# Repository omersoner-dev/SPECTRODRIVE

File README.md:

# 🚀 SpectroDrive – Smart Light Following Robot

SpectroDrive is a multi-functional embedded robotics project integrating sensing, control, and wireless communication into a compact system.

---

## 🎯 Project Overview

This robot is capable of:

* Tracking and following light sources
* Performing interactive LED-based behaviors
* Detecting external disturbances (tilt)
* Securing itself with a password-based system
* Being controlled wirelessly via Bluetooth

---

## ⚙️ System Features

* 🔆 Light Following Mode
* 👋 Greeting Mode (LED animation)
* 🚨 Tilt-based Security System
* 🔐 Dual-stage password protection
* 📡 Bluetooth Control (HC-05)
* 📟 LCD Interface
* 🔊 Buzzer Alert System

---

## 🧩 Project Structure

```text
Firmware/
 └── Arduino/
      └── Spectrodrive.ino

Software/
 └── MobileApp/apk/
      └── Spectrodrive.apk

hardware/
 ├── BOM/
 ├── PCB/
 ├── schematic/
 └── images/
```

---

## 🔧 Hardware

Full hardware design including schematic, PCB, and BOM:

👉 [Hardware Documentation](hardware/README.md)

---

## ⚙️ Firmware

Arduino-based embedded control system:

👉 [Firmware Files](Firmware/Arduino/)

---

## 📱 Mobile Application

Bluetooth-based control interface:

👉 [Mobile App](Software/MobileApp/)

---

## 📸 Preview

### PCB Design

### 3D View

---

## 🛠️ Technologies

* KiCad (PCB & schematic)
* Arduino (Embedded control)
* UART / ADC / GPIO
* Bluetooth (HC-05)

---

## 🎯 Purpose

Developed to gain hands-on experience in:

* Embedded systems
* PCB design
* Robotics integration
* Real-time control systems

---

## 🚀 Future Improvements

* Mobile UI enhancements
* Autonomous navigation
* Advanced control algorithms
* IoT integration

---

## 📌 Author

Electrical & Electronics Engineering student focused on embedded systems and robotics.

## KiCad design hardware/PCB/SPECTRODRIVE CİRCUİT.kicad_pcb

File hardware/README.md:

## 🔧 Hardware Design – SpectroDrive

This section contains the complete hardware design of the SpectroDrive smart robot, including schematic design, PCB layout, and bill of materials.

---

### 🧠 System Overview

The hardware system is built around a microcontroller-based architecture and integrates multiple sensing and control modules:

* Light tracking sensors (LDR)
* Ultrasonic distance sensor (HC-SR04)
* Motor driver (L298N)
* Bluetooth module (HC-05)
* LCD display
* Tilt sensor and buzzer for safety alerts

---

### 📐 Schematic

The schematic includes all sensor interfaces, power distribution, and control logic connections.

---

### 🧩 PCB Layout

Custom PCB was designed in KiCad, including routing, footprint selection, and optimized layout for embedded system integration.

---

### 🧱 3D View

3D visualization of the PCB showing component placement and physical structure.

---

### 📦 Bill of Materials (BOM)

The complete list of components can be found in:

* `BOM/bom.xlsx`
* `BOM/bom.csv`

---

### 🛠️ Design Tools

* KiCad (Schematic & PCB Design)
* Custom libraries for specific modules

---

### 🎯 Notes

This hardware was developed as part of a Teknofest-oriented embedded systems project, focusing on modularity, expandability, and real-world testing.

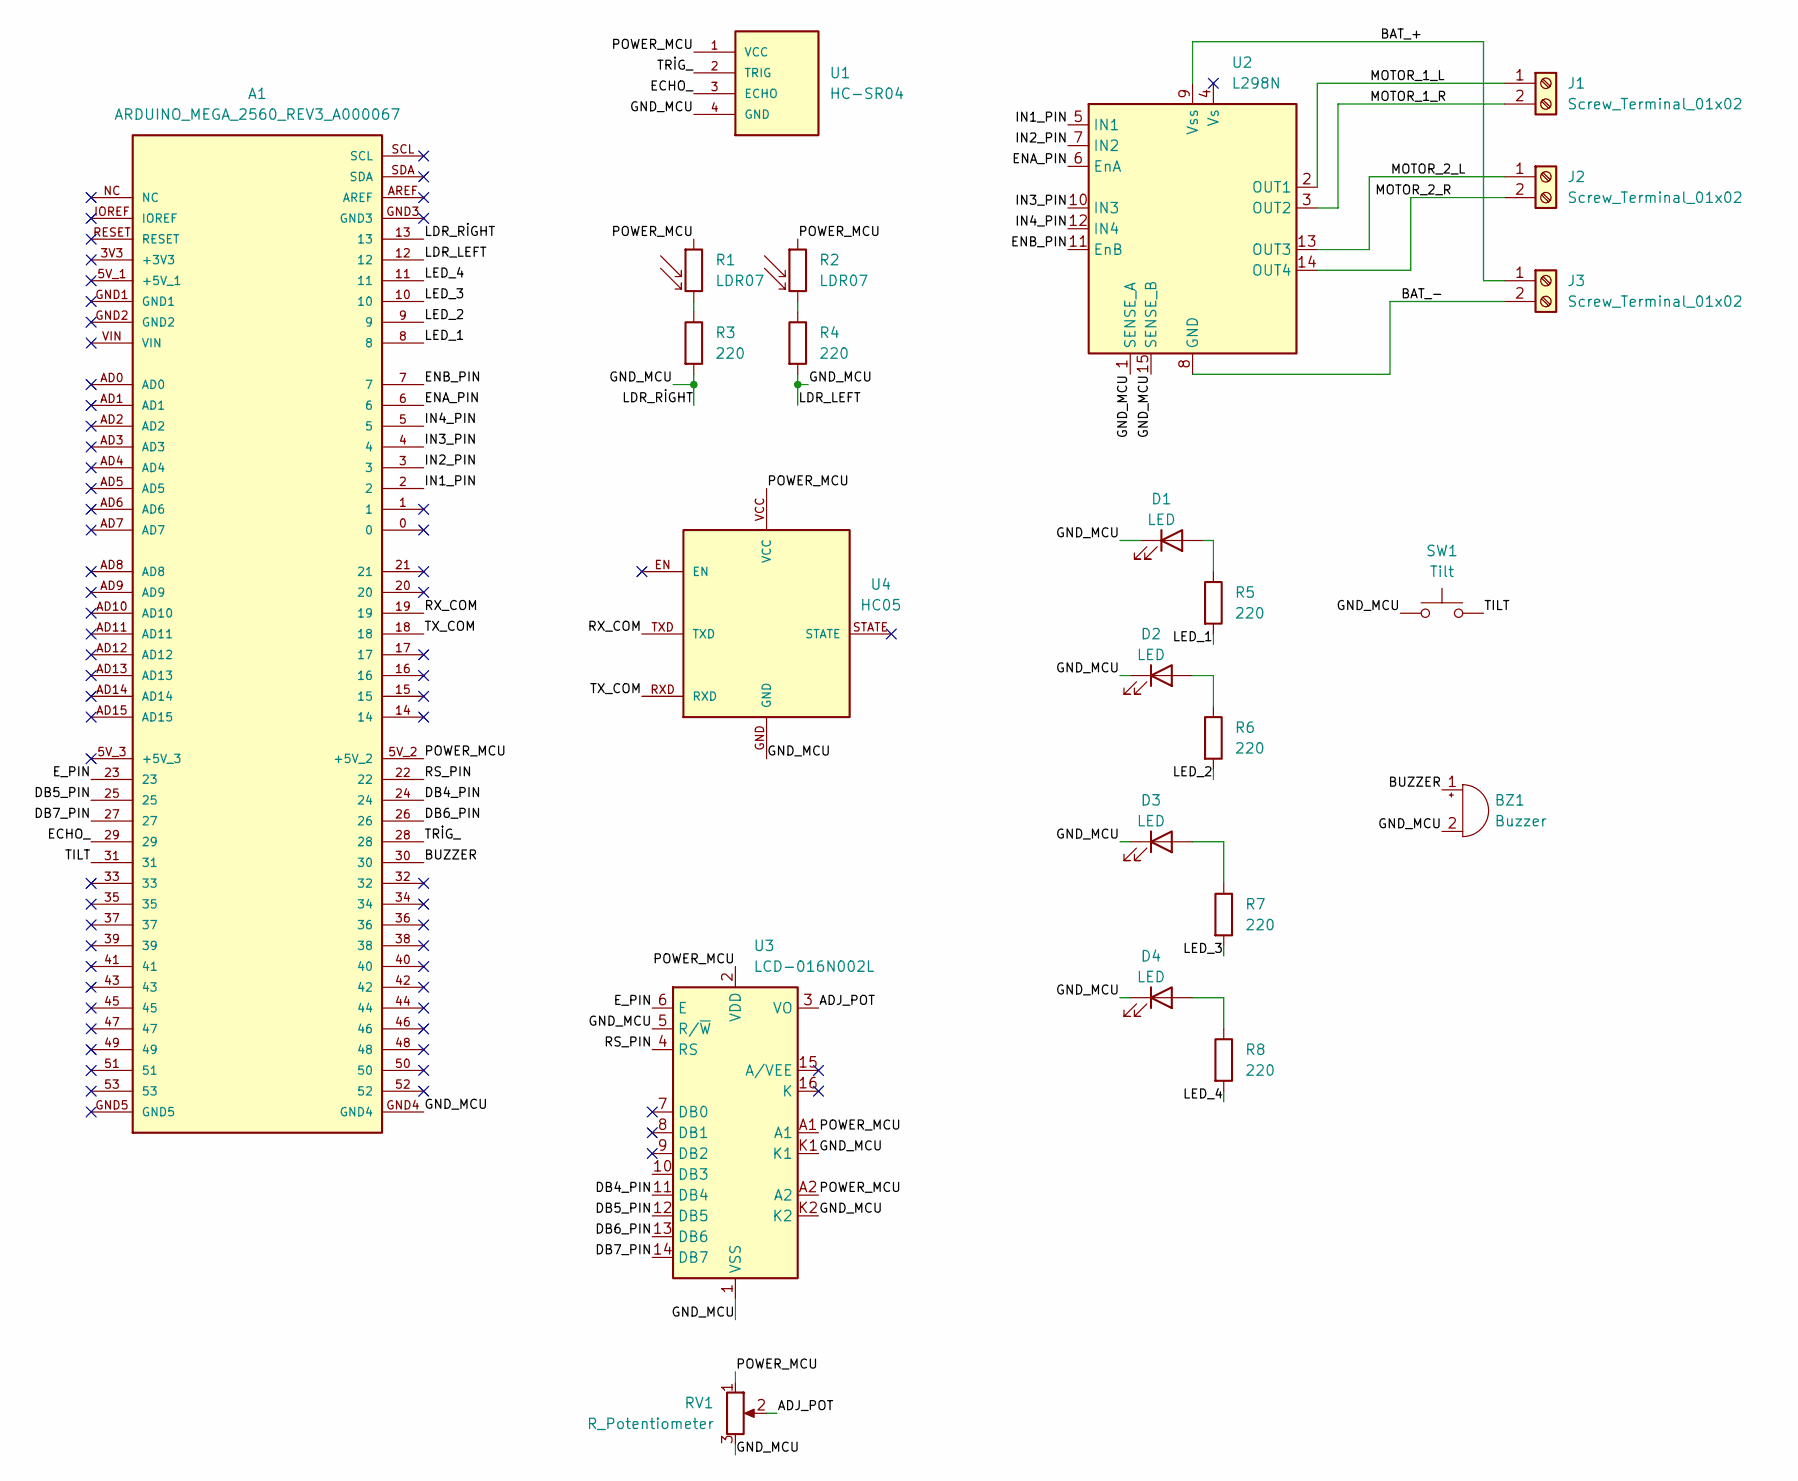
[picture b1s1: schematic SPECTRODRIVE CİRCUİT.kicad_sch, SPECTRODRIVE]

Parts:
A1: ARDUINO_MEGA_2560_REV3_A000067; ARDUINO_ARDUINO_MEGA_2560_REV3_A000067; PARTREV 3
BZ1: Buzzer; Buzzer_12x9.5RM7.6
D1, D2, D3, D4: LED; LED_D8.0mm
J1, J2, J3: Screw_Terminal_01x02; TerminalBlock_bornier-2_P5.08mm
R1, R2: LDR07; R_LDR_5.1x4.3mm_P3.4mm_Vertical
R3, R4, R5, R6, R7, R8: 220; R_Axial_DIN0204_L3.6mm_D1.6mm_P7.62mm_Horizontal
RV1: R_Potentiometer; Potentiometer_Alps_RK163_Single_Horizontal
SW1: Tilt; SW_PUSH_1P1T_6x3.5mm_H5.0_APEM_MJTP1250
U1: HC-SR04; XCVR_HC-SR04
U2: L298N; TO-220-15_P2.54x5.08mm_StaggerOdd_Lead4.58mm_Vertical
U3: LCD-016N002L
U4: HC05

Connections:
/ADJ_POT: RV1.2, U3.3 (VO)
/BAT_+: J3.1, U2.9 (Vss)
/BAT_-: J3.2, U2.8 (GND)
/BUZZER: A1.30, BZ1.1 (+)
/DB4_PIN: A1.24, U3.11 (DB4)
/DB5_PIN: A1.25, U3.12 (DB5)
/DB6_PIN: A1.26, U3.13 (DB6)
/DB7_PIN: A1.27, U3.14 (DB7)
/ECHO_: A1.29, U1.3 (ECHO)
/ENA_PIN: A1.6, U2.6 (EnA)
/ENB_PIN: A1.7, U2.11 (EnB)
/E_PIN: A1.23, U3.6 (E)
/GND_MCU: A1.12, A1.13, A1.GND4, BZ1.2 (-), D1.1 (K), D2.1 (K), D3.1 (K), D4.1 (K), R3.2, R4.2, RV1.3, SW1.1, U1.4 (GND), U2.1 (SENSE_A), U2.15 (SENSE_B), U3.1 (VSS), U3.5 (R/~W), U3.K1, U3.K2, U4.GND
/IN1_PIN: A1.2, U2.5 (IN1)
/IN2_PIN: A1.3, U2.7 (IN2)
/IN3_PIN: A1.4, U2.10 (IN3)
/IN4_PIN: A1.5, U2.12 (IN4)
/LED_1: A1.8, R5.2
/LED_2: A1.9, R6.2
/LED_3: A1.10, R7.2
/LED_4: A1.11, R8.2
/MOTOR_1_L: J1.1, U2.2 (OUT1)
/MOTOR_1_R: J1.2, U2.3 (OUT2)
/MOTOR_2_L: J2.1, U2.13 (OUT3)
/MOTOR_2_R: J2.2, U2.14 (OUT4)
/POWER_MCU: A1.5V_2 (+5V_2), R1.1, R2.1, RV1.1, U1.1 (VCC), U3.2 (VDD), U3.A1, U3.A2, U4.VCC
/RS_PIN: A1.22, U3.4 (RS)
/RX_COM: A1.19, U4.TXD
/TILT: A1.31, SW1.2
/TRİG_: A1.28, U1.2 (TRIG)
/TX_COM: A1.18, U4.RXD
unnamed: D1.2 (A), R5.1
unnamed: D2.2 (A), R6.1
unnamed: D3.2 (A), R7.1
unnamed: D4.2 (A), R8.1
unnamed: R1.2, R3.1
unnamed: R2.2, R4.1

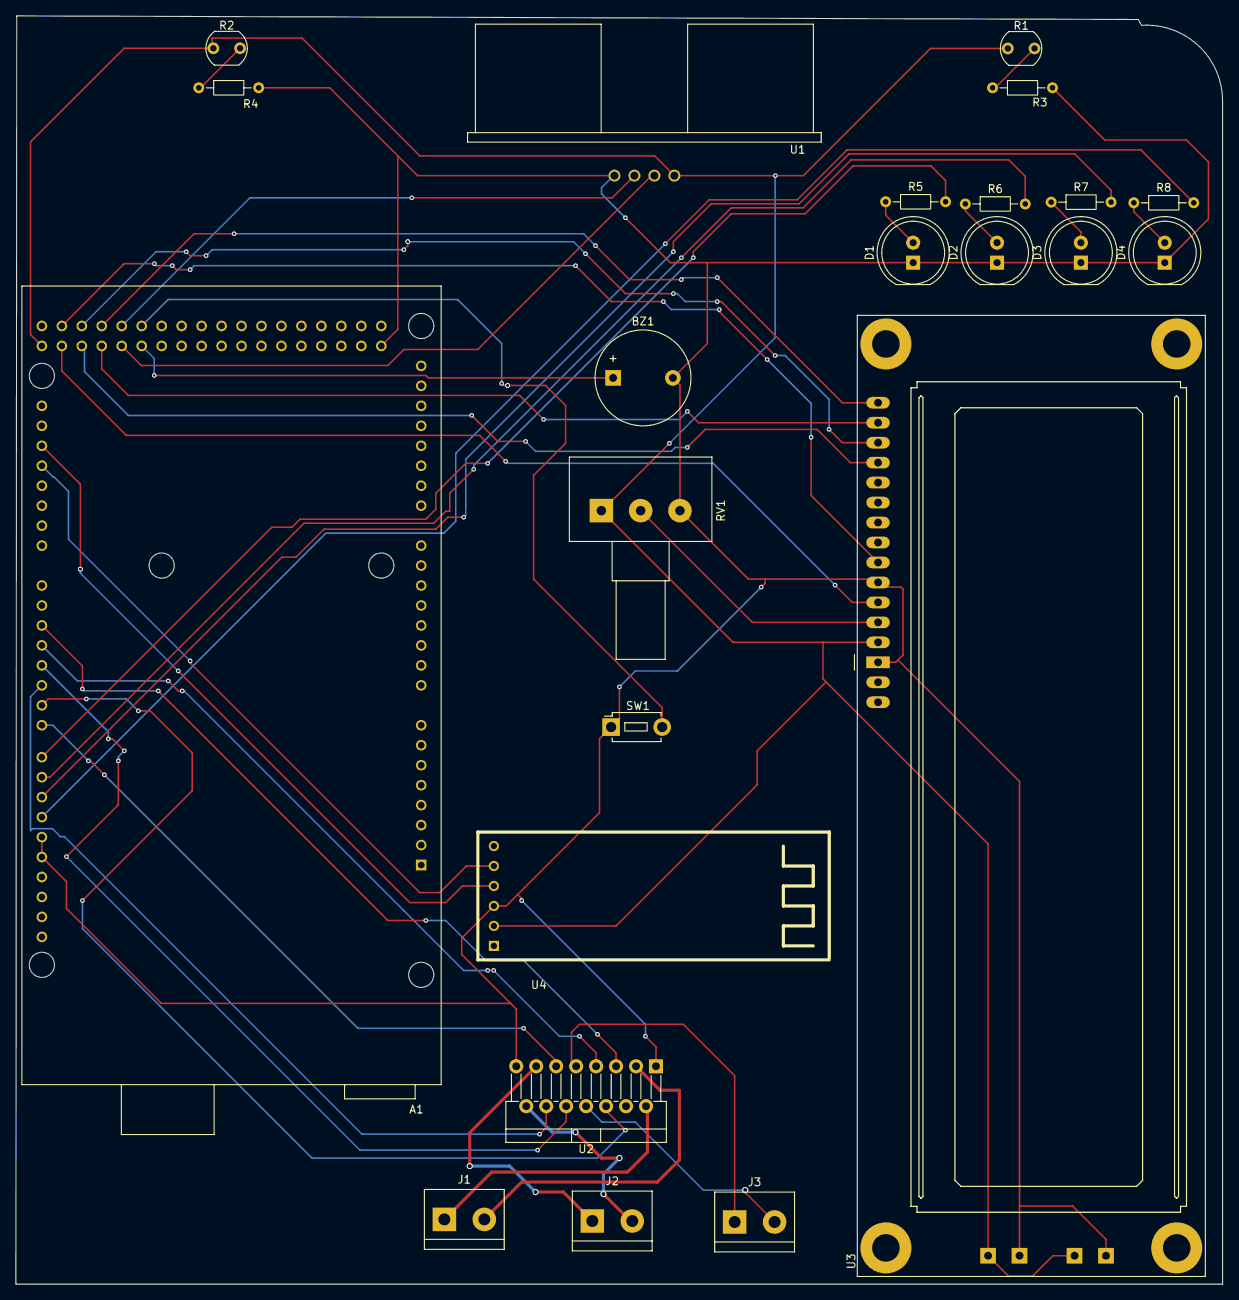
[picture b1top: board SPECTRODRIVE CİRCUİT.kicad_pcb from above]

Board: 2 copper layers, 153.5 x 161.3 mm, 23 parts (0 on the bottom side), 37 nets.

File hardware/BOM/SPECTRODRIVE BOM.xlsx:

Reference | Qty | Value | Footprint | Datasheet
A1 | 1 | ARDUINO_MEGA_2560_REV3_A000067 | MyLibrary:ARDUINO_ARDUINO_MEGA_2560_REV3_A000067
BZ1 | 1 | Buzzer | Buzzer_Beeper:Buzzer_12x9.5RM7.6 | ~
D1-D2-D3-D4 | 4 | LED | LED_THT:LED_D8.0mm | ~
J1-J2-J3 | 3 | Screw_Terminal_01x02 | MyLibrary:TerminalBlock_bornier-2_P5.08mm | ~
R1-R2 | 2 | LDR07 | OptoDevice:R_LDR_5.1x4.3mm_P3.4mm_Vertical | http://www.tme.eu/de/Document/f2e3ad76a925811312d226c31da4cd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
R3-R4-R5-R6-R7-R8 | 6 | 220 | Resistor_THT:R_Axial_DIN0204_L3.6mm_D1.6mm_P7.62mm_Horizontal | ~
RV1 | 1 | R_Potentiometer | Potentiometer_THT:Potentiometer_Alps_RK163_Single_Horizontal | ~
SW1 | 1 | Tilt | Button_Switch_THT:SW_PUSH_1P1T_6x3.5mm_H5.0_APEM_MJTP1250 | ~
U1 | 1 | HC-SR04 | MyLibrary:XCVR_HC-SR04
U2 | 1 | L298N | Package_TO_SOT_THT:TO-220-15_P2.54x5.08mm_StaggerOdd_Lead4.58mm_Vertical | http://www.st.com/st-web-ui/static/active/en/resource/techni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
U3 | 1 | LCD-016N002L | Display:LCD-016N002L | http://www.vishay.com/docs/37299/37299.pdf
U4 | 1 | HC05 | MyLibrary:HC05

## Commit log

2026-03-20 Create schematic
2026-03-20 Rename schematic to README.md
2026-03-20 Rename schematic/README.md to hardware/schematic/README.md
2026-03-23 Rename SPECTRODRIVE CİRCUİT.csv to SPECTRODRIVE BOM.csv
2026-03-23 Create Arduino
2026-03-23 Create a
2026-03-23 Rename sketch_may221b.ino to Spectro.ino
